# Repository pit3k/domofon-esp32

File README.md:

# domofon-esp32 — analog intercom ↔ ESP32-C3 / ESPHome / Home Assistant

An interface that connects a classic **2-wire analog intercom handset line** (Polish: *domofon*) to an
**ESP32-C3 SuperMini (HW-466B)** running **ESPHome**, so the intercom can be used from **Home Assistant**.

> **Status: design only — not yet tested on real hardware.** Schematic, single-sided PCB, BOM and firmware
> are complete; the board has passed KiCad DRC, but nothing has been built or measured yet.

## Features
- **Ring detection** — AC-input optocoupler (LTV-814) on the line, debounced input on GPIO3.
- **Off-hook** — PhotoMOS relay (AQY214EH, 400 V) connects a load resistor and a 600:600 line transformer, just like lifting the handset. The line is forced back on-hook when a configurable limit elapses (default 60 s), whatever took it off-hook.
- **DTMF transmit** — sine PWM ([ESPHome component in this repo](firmware/esphome/components/dtmf_tone)) summed and filtered, coupled through the transformer. Any DTMF sequence; the default sends "1" to open the gate.
- **DTMF receive (software)** — line audio via the transformer to ADC1 (GPIO1), decoded on the ESP with a Goertzel filter bank ([ESPHome component in this repo](firmware/esphome/components/dtmf_decoder)). Works only while off-hook.
- **Galvanic isolation** — ESP ground never touches the line; 4 mm isolation gap + milled slot on the PCB.
- **Extra handset jack** — RJ11 (J1) wired in parallel with the line.

### Home Assistant entities
| Entity | Name | What it does |
|---|---|---|
| `binary_sensor` | Domofon dzwonek | on while someone rings (50 ms on / 1.5 s off filter) |
| `switch` | Domofon otwórz furtkę | sends the DTMF sequence; stays on while the tones play and turns itself off when they finish (does not change off-hook) |
| `text` | Brama - sekwencja DTMF | digits to dial (default `1`; `0-9 * # A-D`, comma = pause) |
| `number` | Brama - czas … | pause before, tone length, inter-digit gap, pause after (defaults 1000 / 200 / 80 / 1000 ms) |
| `switch` | Domofon off-hook | manual off-hook / on-hook (always off after reboot; also forced on-hook by the time limit) |
| `number` | Domofon - maks. czas off-hook | maximum off-hook time, any cause (default 60 s, range 10–3600 s) |
| `event` | Domofon DTMF | fired for every decoded digit (0–9, *, #, A–D) |
| `text_sensor` | Domofon DTMF ostatnia cyfra | last decoded digit |
| `text_sensor` | Domofon DTMF sekwencja | digits concatenated, cleared after 3 s silence or on-hook |

## Schematic

## Repository layout
```
├── README.md
├── docs/
│   ├── design-notes.md          # English summary of the circuit
│   └── design-notes-pl.md       # full design notes (Polish): netlist, pin numbers, rationale
├── hardware/
│   ├── schematic/
│   │   ├── schematic.py         # source (schemdraw)
│   │   └── schematic.svg/.png   # generated output
│   ├── pcb/
│   │   ├── domofon.kicad_pro/.kicad_pcb/.kicad_dru   # KiCad 9 project (single-sided, THT)
│   │   ├── drc-report.txt       # KiCad DRC: 0 violations, 0 unconnected
│   │   ├── README-pl.md         # PCB notes (Polish)
│   │   ├── gerbers/             # Gerber X2 + Excellon (mm) — input for CNC
│   │   ├── previews/            # PNG renders
│   │   └── scripts/             # Python/KiCad generators, autorouting, DRC, export
│   ├── bom/
│   │   ├── bom.csv              # full bill of materials
│   │   └── tme-order.csv        # original TME order (history, pre rev. 5)
│   └── enclosure/               # 3D-printed wall box (CadQuery source, STL, 3MF, STEP, previews)
├── firmware/esphome/
│   ├── domofon.yaml
│   ├── secrets.yaml.example
│   ├── intercom-package.example.yaml   # HA builder example (packages)
│   └── components/
│       ├── dtmf_tone/            # DTMF generation and WAV/TTS playback
│       └── dtmf_decoder/         # DTMF decoding
├── cnc/                         # G-code, operator guide, CAM config & scripts
│   ├── OPERATOR_GUIDE.md       # step-by-step for PrintNC + ioSender (PL)
│   ├── README.md               # CAM overview (EN)
│   ├── cam_config.toml         # feeds, depths, RPM
│   ├── gcode/*.nc              # one file per tool, numbered
│   └── previews/               # toolpath PNGs
└── tools/dtmf_sim.py            # offline simulation of the DTMF decoder algorithm
```

## PCB
- Single-sided (copper on B.Cu only), all parts THT on top, **55.6 × 46.0 mm**, designed for **isolation milling** with a 30° / 0.2 mm V-bit.
- Rules: clearance ≥ 0.4 mm, tracks 0.6 mm (signal) / 1.0 mm (power and line), no vias, **one wire jumper (JP1)**.
- Low parts sit under the ESP32-C3 module → mount the module on female headers (~8–11 mm).
- `gerbers/domofon-F_Cu-jumpers_DO_NOT_MILL.gtl` only models the wire jumper for DRC — **do not mill it**.

| Placement | Bottom copper (mirrored, as milled) |
|---|---|
|  |  |

## How to regenerate
Requirements: Python 3, `schemdraw` + `pillow`; KiCad 9 (`kicad-cli` and the `pcbnew` Python module); `rsvg-convert` (librsvg) for previews; optionally Freerouting 2.x + Java for re-routing.

```bash
# Schematic -> hardware/schematic/schematic.svg + schematic.png
cd hardware/schematic
python3 -m venv .venv && .venv/bin/pip install schemdraw pillow
.venv/bin/python schematic.py

# PCB checks and outputs (run from anywhere)
hardware/pcb/scripts/drc.sh              # DRC -> hardware/pcb/drc-report.txt
hardware/pcb/scripts/export_gerbers.sh   # -> hardware/pcb/gerbers/
hardware/pcb/scripts/make_previews.sh    # -> hardware/pcb/previews/

# Full re-generation of the board from footprints.py / netlist.py / placement.py (optional)
FREEROUTING_JAR=/path/to/freerouting.jar JAVA=java hardware/pcb/scripts/build_and_route.sh 30
#   -> hardware/pcb/work/routed.kicad_pcb ; review, then copy to hardware/pcb/domofon.kicad_pcb
```
Autorouting is not deterministic; the committed `domofon.kicad_pcb` is the reviewed result.

## Firmware
```bash
cd firmware/esphome
cp secrets.yaml.example secrets.yaml   # fill in Wi-Fi credentials
esphome run domofon.yaml
```
The DTMF components are fetched from this repository (`ref: ${git_ref}`, default `main`) by `external_components` in `domofon.yaml`, so no extra files need to be copied.

### Home Assistant (ESPHome builder, recommended)
Create a new device in the HA ESPHome builder and paste [`firmware/esphome/intercom-package.example.yaml`](firmware/esphome/intercom-package.example.yaml). It pulls `domofon.yaml` as a [package](https://esphome.io/components/packages/) from `main` with `refresh: 0s` (re-fetched on every build). Add the secrets from `secrets.yaml.example` to the builder's Secrets. The example configures the device name, API encryption, OTA, Wi-Fi, fallback AP, and captive portal; these device-level settings are kept out of the reusable firmware package. To pin a version, set `git_ref` in `substitutions` to a commit SHA or tag; it selects both `domofon.yaml` and the DTMF components (default `main`). The HA URL defaults to `http://homeassistant.local:8123`; override `ha_url` in `substitutions` if needed.

### Voice prompts (WAV)
Prompts are generated automatically during compilation by the [`dtmf_tone`](firmware/esphome/components/dtmf_tone) component: "wprowadź kod", "drzwi otwarte" and "kod nieprawidłowy" are rendered by Home Assistant's Piper TTS (`tts_get_url` API), and `ringback` is a synthesized 425 Hz tone (1 s on / 4 s off). Add to the builder's Secrets:
```yaml
ha_token: "<long-lived access token>"   # HA profile -> Security -> Long-lived access tokens
```
Results are cached in the build directory, so rebuilds work even if HA is unreachable (the first build needs HA reachable). No WAV files are needed. Voice or language can be changed per clip with `tts: {text, engine, language, voice}`.

Each prompt is a switch ("Domofon głos: …"). Turning it on plays the clip and the switch turns itself off when playback finishes, so an automation can turn it on and wait for `off` instead of watching the diagnostic "Domofon audio aktywne" sensor. The same applies to "Domofon otwórz furtkę" (the DTMF sequence). These switches do not take the line off-hook and do not change the DTMF decoder, except the gate switch, which pauses the decoder for the duration of its own tones. "Domofon sygnał oczekiwania" is the exception: it plays `ringback` in a loop and stays on until something turns it off (a manual turn-off, another clip starting, or hangup — including the off-hook time limit). In YAML: `dtmf_tone.play_wav: {id: dtmf_gen, name: enter_code, loop: false}`; stop with `dtmf_tone.stop`.

## Enclosure
3D-printed flat wall box: 93 × 68 × 26 mm, a base glued to the wall plus a lid held by 4 countersunk M3×10 screws in brass M3 Ø4×4 heat-set inserts. The PCB is flipped (components toward the wall) and shifted +25 mm to the right, leaving a 25.3 mm left chamber.
- Seen from the room: the RJ11 plug sits inside the left chamber (plugged into J1), its flat cable exits through a 5 × 2.5 mm floor slot at the bottom of the left wall (sealed and pinched by a reinforced 5 mm thick plunger on the lid), the USB-C plug goes in from the top, and the wall cable comes in through a Ø12 mm hole in the back plate at (16.0; 15.5) mm.
- Source and print files are in [`hardware/enclosure/`](hardware/enclosure/). The Polish print and assembly guide is in its [README](hardware/enclosure/README.md).

## CNC
Machine: **PrintNC** + Flexi-HAL (**grblHAL**), sender **ioSender**.
Ready G-code lives in [`cnc/gcode/`](cnc/gcode/).
**Operator guide (PL):** [`cnc/OPERATOR_GUIDE.md`](cnc/OPERATOR_GUIDE.md).
Overview / regenerate: [`cnc/README.md`](cnc/README.md).
Do **not** mill `domofon-F_Cu-jumpers_DO_NOT_MILL.gtl` — solder jumper JP1 as a wire on the component side.

## Safety
- **Measure the line first**: idle voltage, ring voltage (DC and AC), off-hook voltage and loop current. Pick R5 to match the original handset's current (typically 20–60 mA).
- Line side is rated for ETSI ES 201 970 / TBR21 ringing (up to 100 Vrms on DC; measured idle 42 V DC): K1 AQY214EH 400 V, TVS D2 P6KE220CA (VRWM 185 V), C5 1 µF/100 V, ring-detect DC-blocking C8 0.47 µF/250 V (replaces the former 4k7 R2, same holes). On-hook the device draws **no DC** (otherwise the exchange sees the line off-hook). Details: [design notes](docs/design-notes.md).
- **Never connect the ESP ground to the intercom line.** Power the ESP from an isolated 5 V USB supply.
- Test on a bench supply through a resistor before connecting to the building installation.
- The intercom is part of the building installation — get the administrator's consent.
- Do not connect J1 to a public telephone line.

## Datasheets
Vendor datasheets are not included in the repo; see e.g.
[Adam Tech MTJ-642BX2](https://app.adam-tech.com/products/download/data_sheet/203851/mtj-642bx2-data-sheet.pdf),
[Bourns LM-NP-1001-B1L](https://www.tme.eu/pl/details/lm-np-1001-b1l/dlawiki/bourns/),
[Liteon LTV-814](https://www.tme.eu/pl/details/ltv-814/transoptory-wyjscie-tranzystorowe/liteon/),
[Panasonic AQY214EH](https://www.tme.eu/en/details/aqy214eh/one-phase-solid-state-relays/panasonic/aqy214eht/),
[Diotec P6KE220CA](https://www.tme.eu/en/details/p6ke220ca-dio/bidirectional-tvs-tht-diodes/diotec-semiconductor/p6ke220ca/),
[WIMA MKS2 1 µF/100 V](https://www.tme.eu/en/details/mks2-1u_100-5%25-r/tht-film-capacitors/wima/mks2d041001k00jo00/).

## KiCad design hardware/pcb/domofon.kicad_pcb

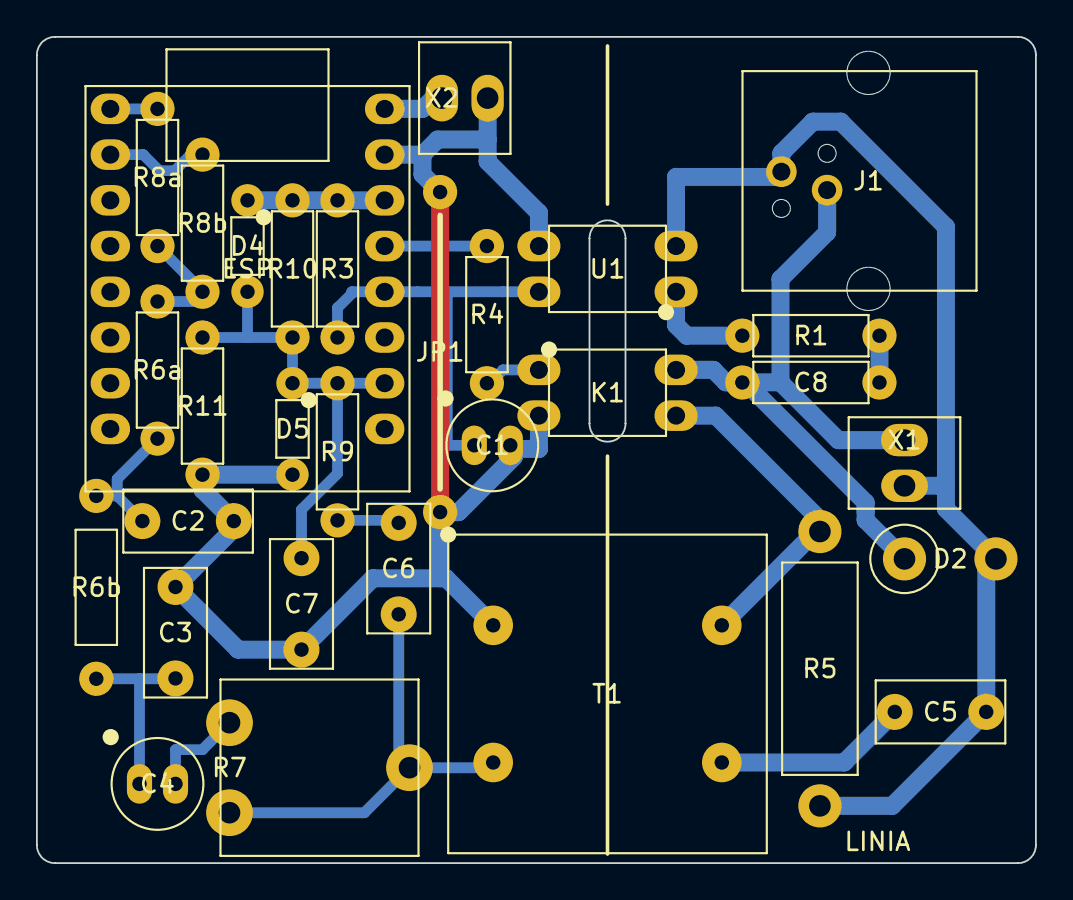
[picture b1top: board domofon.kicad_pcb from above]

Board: 2 copper layers, 55.5 x 45.9 mm, 31 parts (0 on the bottom side), 21 nets.

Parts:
C1: 10u/25V; CP_D5_P2.0
C2, C3, C6: 220n; CFILM_P5.08
C4: 10u/16V NP; CP_D5_P2.0
C5: 1u/100V; CFILM_P5.08
C7: 33n; CFILM_P5.08
C8: 470n/250V; CFILM_P7.62
D2: P6KE220CA; DO15_P5.08_V
D4, D5: BAT85; DO34_P5.08
ESP: ESP32-C3 SuperMini HW-466B; ESP
J1: MTJ-642BX2; MTJ642
JP1: zworka drut; WIRE_P10.16
K1: AQY214EH; DIP4
R1, R10, R11: 4k7; R0207_P7.62
R3: 10k; R0207_P7.62
R4: 330; R0207_P7.62
R5: 330 1W; R0414_P15.24
R6a: 100R; R0207_P7.62
R6b: 100R; R0207_P10.16
R7: 4k7 CA9V; CA9V
R8a, R8b: 330R; R0207_P7.62
R9: 2k2; R0207_P7.62
T1: LM-NP-1001-B1L; T1
U1: LTV-814; DIP4
X1: XY308-2P LINIA; XY308_2P
X2: XY308-2P 5V/GND; XY308_2P

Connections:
+3V3: D4.1, ESP.R3, R3.2, R10.1
+5V: ESP.R1, X2.1
A: R6a.1, R8a.2, R8b.2
B: C2.1, R6a.2, R6b.1
C: C3.1, C4.1, R6b.2
D: C6.1, R7.2, R7.3, T1.4
GND: C1.2, C2.2, C3.2, C7.2, D5.2, ESP.R2, JP1.1, JP1.2, K1.2, R11.2, T1.1, U1.3, X2.2
GPIO1: C7.1, D4.2, D5.1, ESP.R7, R9.2, R10.2, R11.1
GPIO3: C1.1, ESP.R5, R3.1, U1.4
GPIO4: ESP.R4, R4.1
GPIO5: ESP.L1, R8a.1
GPIO6: ESP.L2, R8b.1
H: K1.3, R5.1, T1.8
L1: C8.1, D2.1, J1.2, K1.4, X1.1
L2: C5.2, D2.2, J1.3, R5.2, U1.2, X1.2
N_C4: C4.2, R7.1
N_C6: C6.2, R9.1
N_C8R1: C8.2, R1.1
N_K1A: K1.1, R4.2
N_T1C5: C5.1, T1.5
N_U1A: R1.2, U1.1

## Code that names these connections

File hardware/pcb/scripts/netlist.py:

# Netlist per docs/design-notes-pl.md (schematic v4). Pin-swaps of electrically equivalent pins marked [swap].
NETS = {
 # ---- line side (isolated) ----
 'L1':    [('X1','1'),('J1','2'),('D2','1'),('C8','1'),('K1','4')],
 'L2':    [('X1','2'),('J1','3'),('D2','2'),('U1','2'),('R5','2'),('C5','2')],
 'N_C8R1': [('C8','2'),('R1','1')],
 'N_U1A': [('R1','2'),('U1','1')],
 'H':     [('K1','3'),('R5','1'),('T1','8')],   # [swap] T1 line winding ends 5/8 interchangeable (schematic/docs match PCB: T1.8=H, T1.5=C5)
 'N_T1C5':[('T1','5'),('C5','1')],
 # ---- ESP side ----
 'GND':   [('ESP','R2'),('X2','2'),('U1','3'),('C1','2'),('K1','2'),('C2','2'),('C3','2'),('T1','1'),('R11','2'),('C7','2'),('D5','2'),('JP1','1'),('JP1','2')],
 '+3V3':  [('ESP','R3'),('R3','2'),('R10','1'),('D4','1')],
 '+5V':   [('ESP','R1'),('X2','1')],
 'GPIO3': [('ESP','R5'),('U1','4'),('R3','1'),('C1','1')],
 'GPIO4': [('ESP','R4'),('R4','1')],
 'N_K1A': [('R4','2'),('K1','1')],
 'GPIO5': [('ESP','L1'),('R8a','1')],
 'GPIO6': [('ESP','L2'),('R8b','1')],
 'A':     [('R8a','2'),('R8b','2'),('R6a','1')],
 'B':     [('R6a','2'),('R6b','1'),('C2','1')],
 'C':     [('R6b','2'),('C3','1'),('C4','1')],
 'N_C4':  [('C4','2'),('R7','1')],
 'D':     [('R7','2'),('R7','3'),('T1','4'),('C6','1')],   # [swap] T1 ESP winding ends 1/4 interchangeable (schematic: T1.1=D, T1.4=GND)
 'N_C6':  [('C6','2'),('R9','1')],
 'GPIO1': [('R9','2'),('R10','2'),('R11','1'),('C7','1'),('D4','2'),('D5','1'),('ESP','R7')],
}
LINE_NETS = ['L1','L2','N_C8R1','N_U1A','H','N_T1C5']
POWER_NETS = ['GND','+3V3','+5V']

PARTS = {  # ref: (footprint, value)
 'JP1':('WIRE_P10.16','zworka drut'),
 'ESP':('ESP','ESP32-C3 SuperMini HW-466B'),
 'U1':('DIP4','LTV-814'), 'K1':('DIP4','AQY214EH'), 'T1':('T1','LM-NP-1001-B1L'),
 'R1':('R0207_P7.62','4k7'), 'C8':('CFILM_P7.62','470n/250V'), 'R3':('R0207_P7.62','10k'),
 'R4':('R0207_P7.62','330'), 'R5':('R0414_P15.24','330 1W'),
 'R6a':('R0207_P7.62','100R'), 'R6b':('R0207_P10.16','100R'),
 'R8a':('R0207_P7.62','330R'), 'R8b':('R0207_P7.62','330R'),
 'R9':('R0207_P7.62','2k2'), 'R10':('R0207_P7.62','4k7'), 'R11':('R0207_P7.62','4k7'),
 'R7':('CA9V','4k7 CA9V'),
 'C1':('CP_D5_P2.0','10u/25V'), 'C4':('CP_D5_P2.0','10u/16V NP'),
 'C2':('CFILM_P5.08','220n'), 'C3':('CFILM_P5.08','220n'), 'C7':('CFILM_P5.08','33n'),
 'C6':('CFILM_P5.08','220n'), 'C5':('CFILM_P5.08','1u/100V'),
 'D2':('DO15_P5.08_V','P6KE220CA'), 'D4':('DO34_P5.08','BAT85'), 'D5':('DO34_P5.08','BAT85'),
 'X1':('XY308_2P','XY308-2P LINIA'), 'X2':('XY308_2P','XY308-2P 5V/GND'),
 'J1':('MTJ642','MTJ-642BX2'),
}
